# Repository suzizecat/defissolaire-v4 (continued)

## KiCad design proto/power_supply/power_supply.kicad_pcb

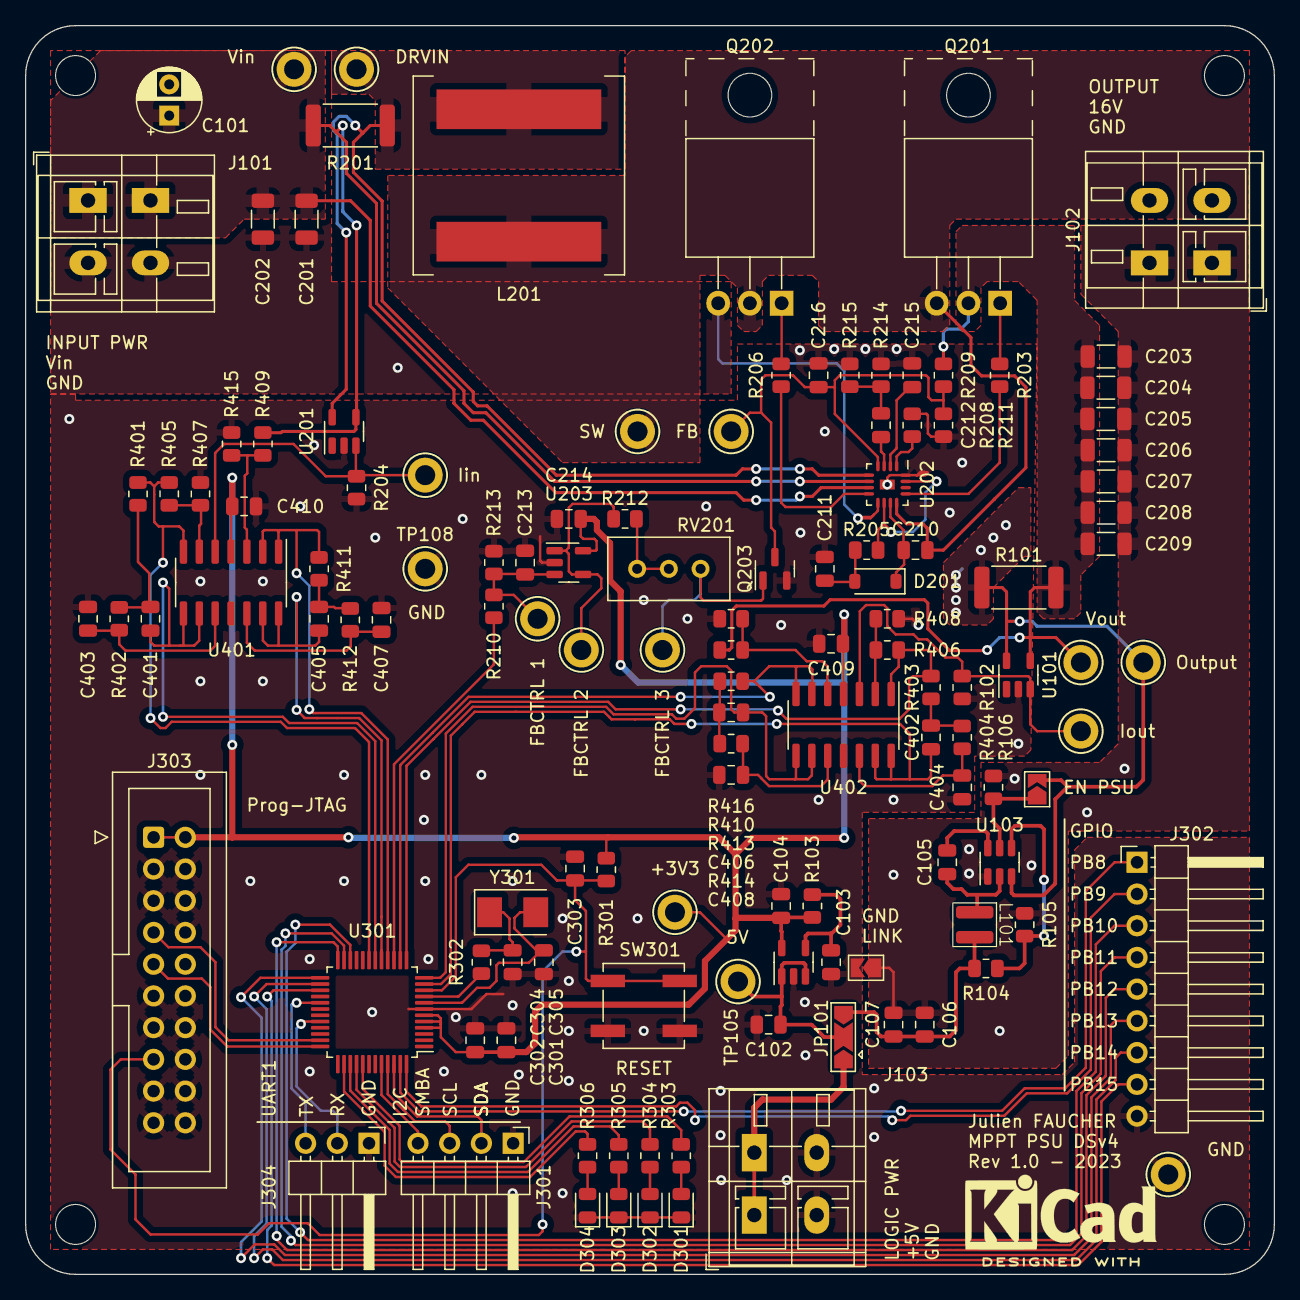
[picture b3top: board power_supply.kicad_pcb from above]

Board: 4 copper layers, 100.0 x 100.0 mm, 130 parts (0 on the bottom side), 81 nets.

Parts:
C101: 47u; CP_Radial_D5.0mm_P2.50mm
C102, C104, C211: 1u; C_0805_2012Metric
C103: 10n; C_0805_2012Metric
C105, C213, C214, C215, C301, C302, C303, C409, C410: 100n; C_0805_2012Metric
C106, C107: 10u; C_0805_2012Metric
C201, C202, C203, C204, C205, C206, C207, C208, C209: 47u; C_1206_3216Metric
C210: 100n/16V; C_0805_2012Metric
C212: 47n; C_0805_2012Metric
C216: 15p; C_0805_2012Metric
C304, C305: C; C_0805_2012Metric
C401, C402, C403, C404, C405, C406, C407, C408: 100p; C_0805_2012Metric
D201: XBS104S14R-G; D_SOD-123
D301, D302, D303, D304: LED; LED_0805_2012Metric
H101, H102, H103, H104: M3; MountingHole_3.2mm_M3
J101, J102, J103: Conn_01x02; TerminalBlock_WAGO_236-402_1x02_P5.00mm_45Degree
J301: Conn_01x04; PinHeader_1x04_P2.54mm_Horizontal
J302: Conn_01x09; PinHeader_1x09_P2.54mm_Horizontal
J303: Conn_ARM_JTAG_SWD_20; IDC-Header_2x10_P2.54mm_Vertical
J304: Conn_01x03; PinHeader_1x03_P2.54mm_Horizontal
JP101: SolderJumper_3_Open; SolderJumper-3_P2.0mm_Open_TrianglePad1.0x1.5mm
JP102: EN DIG SUPPLY; SolderJumper-2_P1.3mm_Open_TrianglePad1.0x1.5mm
JP103: LINK_GND; SolderJumper-2_P1.3mm_Open_TrianglePad1.0x1.5mm
L101: 3.3u; VLS3015CX
L201: 22u; L_Coilcraft_XAL1510-223
Q201, Q202: TK4R3E06PL; TO-220-3_Horizontal_TabUp
Q203: BC846; SOT-23
R101, R201: 8m; R_2512_6332Metric
R102, R204, R209: 12k; R_0805_2012Metric
R103: NM; R_0805_2012Metric
R104: 22k; R_0805_2012Metric
R105: 3.3k; R_0805_2012Metric
R106, R210, R213, R301, R303, R304, R305, R306: 10k; R_0805_2012Metric
R203, R205, R206: 2; R_0805_2012Metric
R208: 470k; R_0805_2012Metric
R211: 1k8; R_0805_2012Metric
R212, R409, R410: 200k; R_0805_2012Metric
R214: 150k; R_0805_2012Metric
R215: 15k; R_0805_2012Metric
R302: 0; R_0805_2012Metric
R401, R402, R403, R404, R405, R406, R407, R408, R411, R412, R413, R414, R416: 33k; R_0805_2012Metric
R415: 100k; R_0805_2012Metric
RV201: 200k (0k); Potentiometer_Bourns_3296W_Vertical
SW301: SW_Push_Dual; SW_SPST_B3SL-1022P
TP101, TP102, TP105, TP106, TP107, TP108, TP201, TP202: TestPoint; TestPoint_Keystone_5010-5014_Multipurpose
TP103: V_{IIN}; TestPoint_Keystone_5010-5014_Multipurpose
TP104: V_{IOUT}; TestPoint_Keystone_5010-5014_Multipurpose
TP203: V_{SW}; TestPoint_Keystone_5010-5014_Multipurpose
TP204: V_{FB}; TestPoint_Keystone_5010-5014_Multipurpose
TP205: V_{CTRL}; TestPoint_Keystone_5010-5014_Multipurpose
TP206: V_{BJT}; TestPoint_Keystone_5010-5014_Multipurpose
TP207: R_{BJT}; TestPoint_Keystone_5010-5014_Multipurpose
U101, U201: ZXCT1110; SOT-23-5
U102: LDK130-33_SOT23_SOT353; SOT-23-5
U103: LMR51430; SOT-23-6
U202: TPS43060; QFN-16_EP_3x3_Pitch0.5mm
U203: TSV911xxLx; SOT-23-5
U301: STM32G051C6Tx; LQFP-48_7x7mm_P0.5mm
U401, U402: TSV914; SOIC-14_3.9x8.7mm_P1.27mm
Y301: 8MHz; Crystal_SMD_5032-2Pin_5.0x3.2mm

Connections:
+3.3V: C104.1, C214.1, C301.1, C302.1, C409.2, C410.2, J303.1 (VTREF), J303.2 (VCC/NC), R103.2, R301.1, TP106.1, U102.5 (OUT), U203.5 (V+), U301.4 (VBAT), U301.5 (VREF+), U301.6 (VDD), U401.4 (V+), U402.4 (V+)
/AlimCTRL: R210.1, U301.15 (DAC1_OUT1)
/Analog Interface/Iin: R204.1, TP103.1, U201.3 (OUT), U401.5 (+)
/Analog Interface/Iin_MEAS: R401.1, R405.2, U301.19 (ADC1_IN8), U401.7
/Analog Interface/Iin_filtered: C401.2, U301.18 (ADC1_IN7), U401.8, U401.9 (-)
/Analog Interface/Iout_MEAS: R403.1, R406.2, U301.13 (ADC1_IN2), U402.1
/Analog Interface/Iout_filtered: C402.2, U301.11 (ADC1_IN0), U402.13 (-), U402.14
/Analog Interface/Vin_MEAS: R411.1, U301.16 (ADC1_IN5), U401.1, U401.2 (-)
/Analog Interface/Vin_filtered: C405.2, U301.17 (ADC1_IN6), U401.13 (-), U401.14
/Analog Interface/Vout_MEAS: R413.1, U301.14 (ADC1_IN3), U402.6 (-), U402.7
/Analog Interface/Vout_filtered: C406.2, U301.12 (ADC1_IN1), U402.8, U402.9 (-)
/Control/I2C_SCL: J301.3, U301.45 (I2C1_SCL)
/Control/I2C_SDA: J301.2, U301.46 (I2C1_SDA)
/Control/I2C_SMBA: J301.4, U301.44 (I2C1_SMBA)
/Control/SWDCLK: J303.9 (TCK/SWDCLK), U301.36 (SYS_SWCLK)
/Control/SWDIO: J303.7 (TMS/SWDIO), U301.35 (SYS_SWDIO)
/Control/~RST: C303.1, J303.15 (~SRST), R301.2, SW301.2, U301.10 (~RST)
/Core/BST: C210.1, D201.1 (K), U202.11 (BOOT)
/Core/DRIVER_VCC: C211.1, D201.2 (A), R205.1
/Core/DRV_VIN: L201.1, R201.1, TP202.1, U201.5 (Vs-), U202.5 (ISNS-)
/Core/FB: C216.1, Q203.3 (C), R209.1, R211.2, TP204.1, U202.4 (FB)
/Core/SW: C210.2, L201.2, Q201.3 (S), Q202.2 (D), TP203.1, U202.12 (SW)
/Iout: R102.1, TP104.1, U101.3 (OUT), U402.3 (+)
/Output: J102.2, JP102.2 (B), R101.1, TP102.1, U101.5 (Vs-), U103.3 (VIN)
/Vin: C101.1, C201.1, C202.1, J101.1, R201.2, R409.1, TP201.1, U201.4 (Vs+), U202.6 (ISNS+), U202.7 (VIN)
/Vout: C203.1, C204.1, C205.1, C206.1, C207.1, C208.1, C209.1, Q201.2 (D), R101.2, R209.2, R410.1, TP101.1, U101.4 (Vs+)
GND: C101.2, C102.2, C103.2, C104.2, C106.2, C107.2, C201.2, C202.2, C203.2, C204.2, C205.2, C206.2, C207.2, C208.2, C209.2, C211.2, C213.2, C214.2, C215.2, C216.2, C301.2, C302.2, C303.2, C304.2, C305.2, C403.2, C404.2, C407.2, C408.2, C409.1, C410.1, D301.1 (K), D302.1 (K), D303.1 (K), D304.1 (K), J101.2, J102.1, J103.2, J301.1, J302.9, J303.3 (~TRST), J303.4 (GND), J303.5 (TDI), J303.6 (GND), J303.8 (GND), J303.10 (GND), J303.11 (RTCK), J303.12 (GND), J303.13 (TDO/SWO), J303.14 (GND), J303.16 (GND), J303.17 (DBGRQ/NC), J303.18 (GND), J303.19 (DBGACK/NC), J303.20 (GND), J304.1, JP103.1 (A), JP103.2 (B), Q202.3 (S), Q203.2 (E), R102.2, R105.1, R106.1, R204.2, R208.2, R211.1, R213.2, R214.2, R215.2, R407.1, R408.1, R415.2, R416.2, SW301.1, TP107.1, TP108.1, U101.2 (GND), U102.2 (GND), U103.1 (GND), U201.2 (GND), U202.9 (PGND), U202.16 (AGND), U202.17 (EP), U203.2 (V-), U301.7 (VSS), U401.11 (V-), U402.11 (V-)
unnamed: C212.2, R214.1, R215.1
unnamed: C304.1, R302.1, Y301.1
unnamed: C401.1, R401.2, R402.1
unnamed: C402.1, R403.2, R404.1
unnamed: C405.1, R411.2, R412.1
unnamed: C406.1, R413.2, R414.1
unnamed: D301.2 (A), R303.2
unnamed: D302.2 (A), R304.2
unnamed: D303.2 (A), R305.2
unnamed: D304.2 (A), R306.2
unnamed: J103.1, JP101.1 (A)
unnamed: J302.1, U301.47 (PB8)
unnamed: J302.2, U301.48 (PB9)
unnamed: J302.3, U301.22 (PB10)
unnamed: J302.4, U301.23 (PB11)
unnamed: J302.5, U301.24 (PB12)
unnamed: J302.6, U301.25 (PB13)
unnamed: J302.7, U301.26 (PB14)
unnamed: J302.8, U301.27 (PB15)
unnamed: J304.2, U301.32 (USART1_RX)
unnamed: J304.3, U301.29 (USART1_TX)
unnamed: C106.1, C107.1, JP101.3 (B), L101.2, R104.2
unnamed: C102.1, JP101.2 (C), TP105.1, U102.1 (IN), U102.3 (EN)
unnamed: JP102.1 (A), R106.2, U103.5 (EN)
unnamed: Q201.1 (G), R203.1
unnamed: Q202.1 (G), R206.2
unnamed: Q203.1 (B), RV201.1, TP206.1
unnamed: R212.2, RV201.2, RV201.3
unnamed: C103.1, R103.1, U102.4 (BP)
unnamed: C105.1, U103.6 (BOOT)
unnamed: R104.1, R105.2, U103.4 (FB)
unnamed: C105.2, L101.1, U103.2 (SW)
unnamed: C212.1, U202.3 (COMP)
unnamed: R205.2, U202.10 (VCC), U202.15 (EN)
unnamed: R203.2, U202.13 (HDRV)
unnamed: R206.1, U202.8 (LDRV)
unnamed: R208.1, U202.1 (RT)
unnamed: C215.1, U202.2 (SS)
unnamed: C213.1, R210.2, R213.1, TP205.1, U203.3 (+)
unnamed: R212.1, TP207.1, U203.1, U203.4 (-)
unnamed: R306.1, U301.38 (PD0)
unnamed: R305.1, U301.39 (PD1)
unnamed: R304.1, U301.40 (PD2)
unnamed: R303.1, U301.41 (PD3)
unnamed: C305.1, U301.8 (RCC_OSC_IN), Y301.2
unnamed: R302.2, U301.9 (RCC_OSC_OUT)
unnamed: R409.2, R415.1, U401.3 (+)
unnamed: R405.1, R407.2, U401.6 (-)
unnamed: C403.1, R402.2, U401.10 (+)
unnamed: C407.1, R412.2, U401.12 (+)
unnamed: R406.1, R408.2, U402.2 (-)
unnamed: R410.2, R416.1, U402.5 (+)
unnamed: C408.1, R414.2, U402.10 (+)
unnamed: C404.1, R404.2, U402.12 (+)

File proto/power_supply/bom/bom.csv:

"#","Reference","Qty","Value","Footprint","DNP","MPN","Mouser SKU"
"1","C102, C104","2","1u","Capacitor_SMD:C_0805_2012Metric","","",""
"2","C103, C401, C402, C403, C404, C405, C406, C407, C408","9","10n","Capacitor_SMD:C_0805_2012Metric","","",""
"3","C105, C210, C213, C214, C215, C301, C302, C303, C409, C410","10","100n","Capacitor_SMD:C_0805_2012Metric","","0805YC104M4T2A ","581-0805YC104M4T2A "
"4","C106, C107","2","10u","Capacitor_SMD:C_0805_2012Metric","","",""
"5","C201, C202, C203, C204, C205, C206, C207, C208, C209","9","47u","Capacitor_SMD:C_1206_3216Metric","","C3216X5R1E476M160AC","810-C3216X5R1E476M "
"6","C211","1","1u/10V","Capacitor_SMD:C_0805_2012Metric","","",""
"7","C212","1","47n","Capacitor_SMD:C_0805_2012Metric","","",""
"8","D201","1","XBS104S14R-G","Diode_SMD:D_SOD-123","","XBS104S14R-G"," 865-XBS104S14R-G "
"9","HS201, HS202","2","HSE-B2111-038","","","HSE-B2111-038"," 490-HSE-B2111-038 "
"10","L101","1","3.3u","power_supply:VLS3015CX","","VLS3015CX-3R3M-1","810-VLS3015CX3R3M1 "
"11","L201","1","22u","Inductor_SMD:L_Coilcraft_XAL1510-223","","XAL1510-223MED","994-XAL1510-223MED "
"12","Q201, Q202","2","TK4R3E06PL","Package_TO_SOT_THT:TO-220-3_Horizontal_TabUp","","TK4R3E06PL"," 757-TK4R3E06PLS1X "
"13","Q203","1","BC846","Package_TO_SOT_SMD:SOT-23","","BC846BLT1G"," 863-BC846BLT1G "
"14","R101, R201","2","8m","Resistor_SMD:R_2512_6332Metric","","PA2512FKE7W0R016E","603-PA2512FKE7W0R16E "
"15","R102, R204, R209","3","12k","Resistor_SMD:R_0805_2012Metric","","",""
"16","R104","1","22k","Resistor_SMD:R_0805_2012Metric","","",""
"17","R105","1","3.3k","Resistor_SMD:R_0805_2012Metric","","",""
"18","R106, R210, R213, R301, R303, R304, R305, R306","8","10k","Resistor_SMD:R_0805_2012Metric","","",""
"19","R203, R205, R206","3","2","Resistor_SMD:R_0805_2012Metric","","CHP0805QFW-2R00ELF","652-CHP0805QFW-2R00ELF"
"20","R208","1","470k","Resistor_SMD:R_0805_2012Metric","","",""
"21","R211","1","1k8","Resistor_SMD:R_0805_2012Metric","","",""
"22","R212, R409, R410","3","200k","Resistor_SMD:R_0805_2012Metric","","",""
"23","R214","1","150k","Resistor_SMD:R_0805_2012Metric","","",""
"24","R215","1","15k","Resistor_SMD:R_0805_2012Metric","","",""
"25","R401, R402, R403, R404, R411, R412, R413, R414","8","6.8k","Resistor_SMD:R_0805_2012Metric","","",""
"26","R405, R406, R407, R408, R416","5","33k","Resistor_SMD:R_0805_2012Metric","","",""
"27","R415","1","100k","Resistor_SMD:R_0805_2012Metric","","",""
"28","RV201","1","200k (0k)","Potentiometer_THT:Potentiometer_Bourns_3296W_Vertical","","3296W-1-204LF"," 652-3296W-1-204LF "
"29","SW301","1","B3SL-1022P","Button_Switch_SMD:SW_SPST_B3SL-1022P","","B3SL-1022P"," 653-B3SL-1022P "
"30","U101, U201","2","ZXCT1110","Package_TO_SOT_SMD:SOT-23-5","","ZXCT1110W5-7"," 522-ZXCT1110W5-7 "
"31","U102","1","LDK130M33R","Package_TO_SOT_SMD:SOT-23-5","","LDK130M33R"," 511-LDK130M33R "
"32","U103","1","LMR51430","Package_TO_SOT_SMD:SOT-23-6","","LMR51430YDDCR"," 595-LMR51430YDDCR "
"33","U202","1","TPS43060","power_supply:QFN-16_EP_3x3_Pitch0.5mm","","TPS43060"," 595-TPS43060RTER "
"34","U203","1","TSV911xxLx","Package_TO_SOT_SMD:SOT-23-5","","TSV911ILT"," 511-TSV911ILT "
"35","U301","1","STM32G051C6Tx","Package_QFP:LQFP-48_7x7mm_P0.5mm","","STM32G051C6T6"," 511-STM32G051C6T6 "
"36","U401, U402","2","TSV914","Package_SO:SOIC-14_3.9x8.7mm_P1.27mm","","TSV914IDT"," 511-TSV914IDT "

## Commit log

2023-01-06 [ALIM] Update base alims
2023-03-14 Global alimentation update
2023-03-24 Calculs pour gate drive
2023-03-24 Add maths for gate drive
2023-03-27 Finish alim sch, start PCB
2023-03-27 Update PCB
2023-03-29 Finish first routing
2023-03-29 Update planes and fix DRC
2023-03-29 Improve overall
2023-03-31 Update with additional PSU from output
2023-04-03 Document PCB
2023-04-03 Final edit before v1 release
2023-04-08 Update for BOM
2023-04-18 [PCB] Elaborate BOM
2023-06-06 Start overall new board
2023-06-06 Update overall power scheme
2023-11-22 Start design of new PSU
2023-11-22 Update components values
2023-11-24 [PSU] Compute values for LT8710 PSU
2023-11-25 Fix permission (NTFS)
2024-02-19 PSU should be OK
2024-02-23 Progresses
2024-03-08 Update schematics
2024-04-02 Some work
2024-04-09 Update, with FTDI, mostly OK
2024-04-11 Finalize schema for bat charger
2024-04-12 Finalize sch and start component mapping
2024-04-16 update BOM
2024-04-16 BOM OK
2024-04-17 Start route PCB
2024-04-19 Route of power rails
2024-04-21 Power routed
2024-04-23 Start re-doing routing
2024-04-23 Rework north route
2024-04-23 Finished redoing power routing
2024-04-24 More routing
2024-04-25 Routing done.
2024-04-25 WIP cleanup silkscreen
    Pre-page numbering
2024-04-25 Clean silkscreen
2024-04-25 Tapeout
2024-04-29 Sent to fab
2024-04-29 BOM almost OK, starts new side board.
2024-04-30 Revised with BOM ordered
2024-05-11 Start soft with vscode and STM32 extension
2024-05-16 Remove modules for debugging
2024-05-16 Reintegrate modules
